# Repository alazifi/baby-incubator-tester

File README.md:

# BABY INCUBATOR TESTER
Proyek ini merupakan kerjasama antara PT. Hana Master Jaya dan PT. Fania Ersa Pratama untuk membuat suatu alat yang digunakan di bidang medis dengan fungsi untuk mengkalibrasi inkubator bayi.

# KOMPATIBILITAS VERSI
<sup>Untuk detail panduan pengelolaan versi [klik disini.](Panduan_Pengelolaan_Versi.md)</sup>

Berikut pasangan versi yang diimplementasikan untuk menghasilkan kinerja alat yang optimal.

| Versi Perangkat |                                 Elektrik                                 |                                     HMI                                      | Koding                                                                    | Mekanik |
|:---------------:|:------------------------------------------------------------------------:|:----------------------------------------------------------------------------:|---------------------------------------------------------------------------|---------|
|   Belum Rilis   | [V5.0.0](Hardware_Development/02_Schematics_and_PCB/PCB_Utama.md#v500-belum-dirilis) | [V3.0.0](Hardware_Development/04_Nextion_HMI/Kode_HMI.md#v300-belum-dirilis) | [V4.0.0](Hardware_Development/03_Code/Kode_Arduino.md#v400-belum-dirilis) | -       |
|     Versi 4     |                                    -                                     |                                      -                                       | -                                                                         | -       |
|     Versi 3     |                                    -                                     |                                      -                                       | -                                                                         | -       |
|     Versi 2     |                                    -                                     |                                      -                                       | -                                                                         | -       |
|     Versi 1     |                                    -                                     |                                      -                                       | -                                                                         | -       |

Untuk dokumentasi skematik dan PCB bisa [klik disini](Hardware_Development/02_Schematics_and_PCB/PCB_Utama.md)!

Untuk dokumentasi koding Arduino bisa [klik disini](Hardware_Development/03_Code/Kode_Arduino.md)!

Untuk dokumentasi UI dari HMI Nextion bisa [klik disini](Hardware_Development/04_Nextion_HMI/Desain_HMI.md)!

## Struktur Direktori Proyek

```bash
project/
│
├── Assembly and Instructions/          # Dokumen untuk produksi
│ ├── 01_Working_Instruction/           # Instruksi untuk produksi
│ └── 02_Checklists/                    # Inspeksi komponen produksi
│
├── Design and Research/                # Data-data terkait riset dalam pengembangan
│ ├── 01_Design_Documents/              # Data rujukan riset dan pengembangan
│ └── 02_Research_Notes/                # Perhitungan nilai komponen
│
├── Final Documentations/               # Dokumentasi terkait pengguna akhir
│ ├── 01_Final_Reports/                 # Laporan akhir setelah produksi
│ ├── 02_User_Manual/                   # Panduan pengguna
│ └── 03_Additional_Resources/          # Sumber tambahan
│
├── Hardware Development/               # Pengembangan terkait perangkat keras
│ ├── 01_BoM_List/                      # Harga pembelian komponen
│ ├── 02_Schematics_and_PCB/            # Desain komponen elektronik
│ ├── 03_Code/                          # Kode firmware untuk PCB
│ └── 04_Nextion_HMI/                   # Desain dan kode untuk HMI
│
├── Past Documents/                     # Data terdahulu sebelum Mei 2023
│
├── Project Management/                 # Manajemen proyek Data-data terkait riset dalam pengembangan
│ ├── 01_Project_Plan/                  # Perencanaan pengerjaan proyek
│ ├── 02_Meetings/                      # Rapat dalam pengerjaan proyek
│ └── 03_Documents/                     # Dokumen terkait manajemen proyek seperti MoM
│
├── Testing and Validation/             # Data-data terkait hasil uji
│ ├── 01_Battery_Testing/               # Data uji baterai
│ ├── 02_Device_Testing/                # Data uji perangkat
│ └── 03_QC_Reports/                    # Laporan QC
│ 
└── README.md # Informasi proyek secara umum, kamu lagi disini!
```
- - - -

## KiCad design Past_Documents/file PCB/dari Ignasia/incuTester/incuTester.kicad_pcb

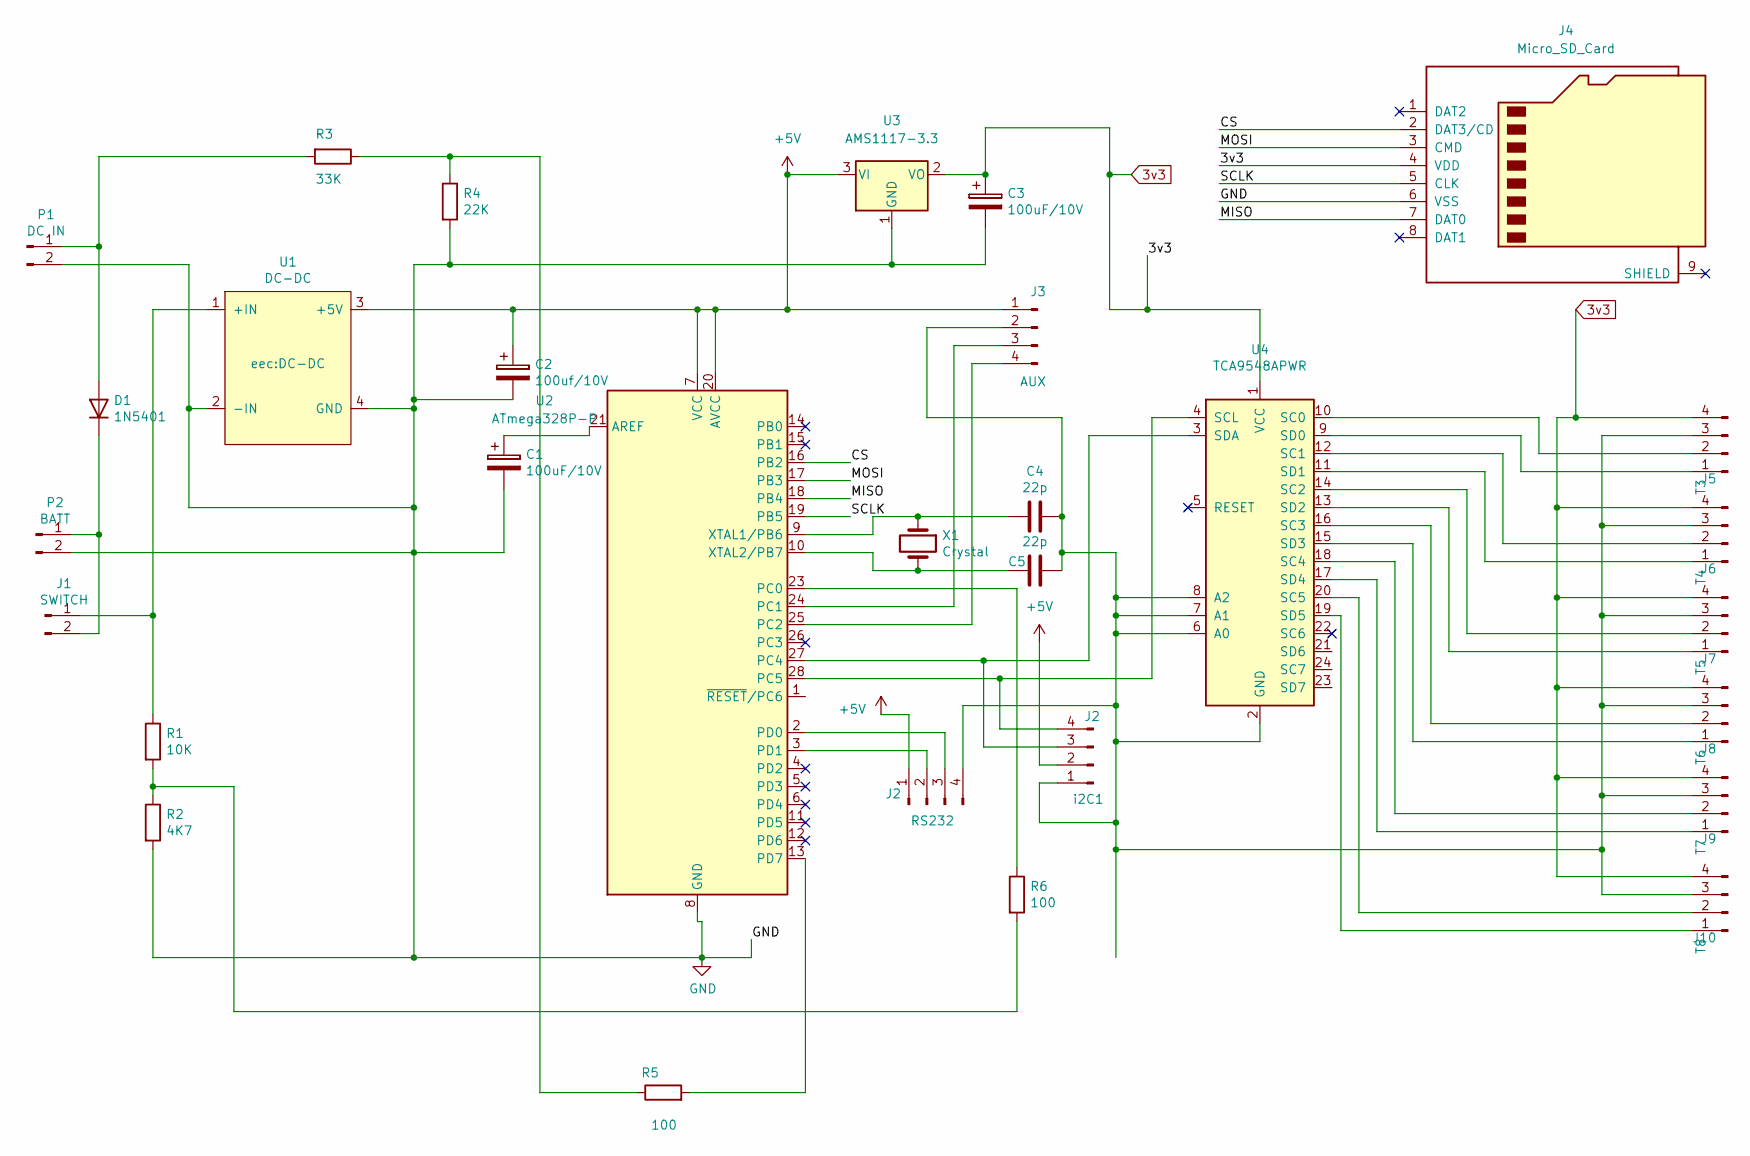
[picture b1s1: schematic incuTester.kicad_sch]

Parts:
C1, C3: 100uF/10V; CP_Radial_D8.0mm_P3.50mm
C2: 100uf/10V; CP_Radial_D8.0mm_P3.50mm
C4, C5: 22p; C_Disc_D3.0mm_W2.0mm_P2.50mm
D1: 1N5401; D_DO-201AD_P15.24mm_Horizontal
J1: SWITCH; PinHeader_1x02_P2.54mm_Vertical
J2: RS232; PinHeader_1x04_P2.54mm_Vertical
J3: AUX; PinHeader_1x04_P2.54mm_Vertical
J4: Micro_SD_Card; microSD_HC_Hirose_DM3AT-SF-PEJM5
J5: T3; PinHeader_1x04_P2.54mm_Vertical
J6: T4; PinHeader_1x04_P2.54mm_Vertical
J7: T5; PinHeader_1x04_P2.54mm_Vertical
J8: T6; PinHeader_1x04_P2.54mm_Vertical
J9: T7; PinHeader_1x04_P2.54mm_Vertical
J10: T8; PinHeader_1x04_P2.54mm_Vertical
P1: DC IN; PinHeader_1x02_P2.54mm_Vertical
P2: BATT; PinHeader_1x02_P2.54mm_Vertical
R1: 10K; R_Axial_DIN0207_L6.3mm_D2.5mm_P10.16mm_Horizontal
R2: 4K7; R_Axial_DIN0207_L6.3mm_D2.5mm_P10.16mm_Horizontal
R3: 33K; R_Axial_DIN0207_L6.3mm_D2.5mm_P10.16mm_Horizontal
R4: 22K; R_Axial_DIN0207_L6.3mm_D2.5mm_P10.16mm_Horizontal
R5, R6: 100; R_Axial_DIN0207_L6.3mm_D2.5mm_P10.16mm_Horizontal
U1: DC-DC
U2: ATmega328P-P; DIP-28_W7.62mm
U3: AMS1117-3.3; SOT-223-3_TabPin2
U4: TCA9548APWR; DIP-24_W15.24mm_LongPads
X1: Crystal; Crystal_HC18-U_Vertical
i2C1: J2; PinHeader_1x04_P2.54mm_Vertical

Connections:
3v3: C3.1, J4.4 (VDD), J5.4, J6.4, J7.4, J8.4, J9.4, J10.4, U3.2 (VO), U4.1 (VCC)
+5V: C2.1, J2.1, J3.1, U1.3 (+5V), U2.7 (VCC), U2.20 (AVCC), i2C1.2; also elsewhere on the board
/CS: J4.2 (DAT3/CD), U2.16 (PB2)
/MISO: J4.7 (DAT0), U2.18 (PB4)
/MOSI: J4.3 (CMD), U2.17 (PB3)
/SCLK: J4.5 (CLK), U2.19 (PB5)
unnamed: D1.2 (A), P1.1, R3.2
unnamed: D1.1 (K), J1.2, P2.1
unnamed: J1.1, R1.1, U1.1 (+IN)
unnamed: J2.2, U2.3 (PD1)
unnamed: J2.3, U2.2 (PD0)
unnamed: J3.3, U2.24 (PC1)
unnamed: J3.4, U2.25 (PC2)
unnamed: J5.1, U4.9 (SD0)
unnamed: J5.2, U4.10 (SC0)
unnamed: J6.1, U4.11 (SD1)
unnamed: J6.2, U4.12 (SC1)
unnamed: J7.1, U4.13 (SD2)
unnamed: J7.2, U4.14 (SC2)
unnamed: J8.1, U4.15 (SD3)
unnamed: J8.2, U4.16 (SC3)
unnamed: J9.1, U4.17 (SD4)
unnamed: J9.2, U4.18 (SC4)
unnamed: J10.1, U4.19 (SD5)
unnamed: J10.2, U4.20 (SC5)
unnamed: R1.2, R2.1, R6.2
unnamed: R3.1, R4.1, R5.1
unnamed: C1.1, U2.21 (AREF)
unnamed: R6.1, U2.23 (PC0)
unnamed: U2.27 (PC4), U4.3 (SDA), i2C1.3
unnamed: U2.28 (PC5), U4.4 (SCL), i2C1.4
unnamed: R5.2, U2.13 (PD7)
unnamed: C4.1, U2.9 (XTAL1/PB6), X1.1
unnamed: C5.1, U2.10 (XTAL2/PB7), X1.2
RST: U2.1 (~RESET/PC6); also elsewhere on the board

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
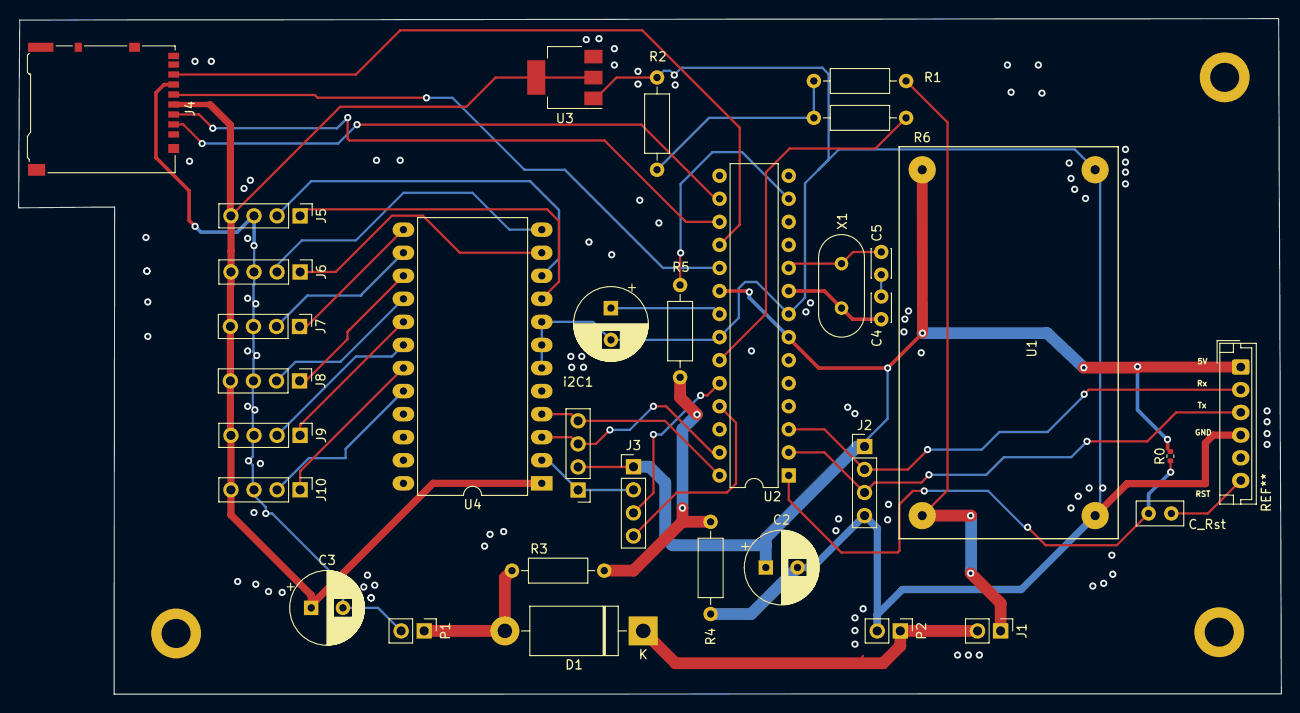
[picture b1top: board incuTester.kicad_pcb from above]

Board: 2 copper layers, 139.1 x 74.4 mm, 32 parts (0 on the bottom side), 36 nets.

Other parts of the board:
C_Rst: 0.1uF/10V; C_Disc_D5.0mm_W2.5mm_P2.50mm
R0: 10k; R_0402_1005Metric

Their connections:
+5V: R0.2; also elsewhere on the board
RST: C_Rst.1, R0.1; also elsewhere on the board

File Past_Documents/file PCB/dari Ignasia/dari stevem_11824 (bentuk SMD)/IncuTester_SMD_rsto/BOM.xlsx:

Column1 | Column2 | Column3 | Column4 | Column5 | Column6 | Column7 | Column8 | Column9 | Column10
Date: | 29/11/2023 08:27:42
Tool: | Eeschema 7.0.6
Generator: | C:\Program Files\KiCad\7.0\bin\scripting\plugins/bom_csv_grouped_by_value.py
Component Count: | 30
Collated Components:
Item | Manufacturer Part | Manufacturer / Supplier | Qty | Reference(s) | Value | LibPart | Footprint | Datasheet | Link
1 | 04EC2054 | KNSCHA | 2 | C1, C3 | 100uF/10V | INCUersa-rescue:CP-Device | Capacitor_THT:CP_Radial_D8.0mm_P3.50mm
2 | 04EC2054 | KNSCHA | 1 | C2 | 100uf/10V | INCUersa-rescue:CP-Device | Capacitor_THT:CP_Radial_D8.0mm_P3.50mm
3 | CC1H220KA1EDCH4B1100 | Dersonic | 2 | C4, C5 | 22p | Device:C | Capacitor_THT:C_Disc_D3.0mm_W2.0mm_P2.50mm | ~
4 | 1N5401 | MDD (Microdiode Electronics) | 1 | D1 | 1N5401 | Diode:1N5401 | Diode_THT:D_DO-201AD_P15.24mm_Horizontal | http://www.vishay.com/docs/88516/1n5400.pdf
5 | B4B-XH-A(LF)(SN) | JST | 1 | i2C1 | J2 | Connector:Conn_01x04_Male | Connector_PinHeader_2.54mm:PinHeader_1x04_P2.54mm_Vertical | ~
6 | B2B-XH-A(LF)(SN) | JST | 1 | J1 | SWITCH | Connector:Conn_01x02_Male | Connector_PinHeader_2.54mm:PinHeader_1x02_P2.54mm_Vertical | ~
7 | B4B-XH-A(LF)(SN) | JST | 1 | J2 | RS232 | Connector:Conn_01x04_Male | Connector_PinHeader_2.54mm:PinHeader_1x04_P2.54mm_Vertical | ~
8 | B4B-XH-A(LF)(SN) | JST | 1 | J3 | AUX | Connector:Conn_01x04_Male | Connector_PinHeader_2.54mm:PinHeader_1x04_P2.54mm_Vertical | ~
9 | DM3AT-SF-PEJM5 | Hirose | 1 | J4 | Micro_SD_Card | Connector:Micro_SD_Card | Connector_Card:microSD_HC_Hirose_DM3AT-SF-PEJM5 | http://katalog.we-online.de/em/datasheet/693072010801.pdf
10 | B4B-XH-A(LF)(SN) | JST | 1 | J5 | T3 | Connector:Conn_01x04_Male | Connector_PinHeader_2.54mm:PinHeader_1x04_P2.54mm_Vertical | ~
11 | B4B-XH-A(LF)(SN) | JST | 1 | J6 | T4 | Connector:Conn_01x04_Male | Connector_PinHeader_2.54mm:PinHeader_1x04_P2.54mm_Vertical | ~
12 | B4B-XH-A(LF)(SN) | JST | 1 | J7 | T5 | Connector:Conn_01x04_Male | Connector_PinHeader_2.54mm:PinHeader_1x04_P2.54mm_Vertical | ~
13 | B4B-XH-A(LF)(SN) | JST | 1 | J8 | T6 | Connector:Conn_01x04_Male | Connector_PinHeader_2.54mm:PinHeader_1x04_P2.54mm_Vertical | ~
14 | B4B-XH-A(LF)(SN) | JST | 1 | J9 | T7 | Connector:Conn_01x04_Male | Connector_PinHeader_2.54mm:PinHeader_1x04_P2.54mm_Vertical | ~
15 | B4B-XH-A(LF)(SN) | JST | 1 | J10 | T8 | Connector:Conn_01x04_Male | Connector_PinHeader_2.54mm:PinHeader_1x04_P2.54mm_Vertical | ~
16 | B2B-XH-A(LF)(SN) | JST | 1 | P1 | DC IN | Connector:Conn_01x02_Male | Connector_PinHeader_2.54mm:PinHeader_1x02_P2.54mm_Vertical | ~
17 | B2B-XH-A(LF)(SN) | JST | 1 | P2 | BATT | Connector:Conn_01x02_Male | Connector_PinHeader_2.54mm:PinHeader_1x02_P2.54mm_Vertical | ~
18 | Resistor 10kOhm, minimal 100mW, THT |  | 1 | R1 | 10K | Device:R | Resistor_THT:R_Axial_DIN0207_L6.3mm_D2.5mm_P10.16mm_Horizontal | ~
19 | Resistor 4700Ohm, minimal 100mW, THT |  | 1 | R2 | 4K7 | Device:R | Resistor_THT:R_Axial_DIN0207_L6.3mm_D2.5mm_P10.16mm_Horizontal | ~
20 | Resistor 33kOhm, minimal 250mW, THT |  | 1 | R3 | 33K | Device:R | Resistor_THT:R_Axial_DIN0207_L6.3mm_D2.5mm_P10.16mm_Horizontal | ~
21 | Resistor 22kOhm, minimal 250mW, THT |  | 1 | R4 | 22K | Device:R | Resistor_THT:R_Axial_DIN0207_L6.3mm_D2.5mm_P10.16mm_Horizontal | ~
22 | Resistor 100Ohm, minimal 100mW, THT |  | 2 | R5, R6 | 100 | Device:R | Resistor_THT:R_Axial_DIN0207_L6.3mm_D2.5mm_P10.16mm_Horizontal | ~
23 | LM2596S DC To DC Buck Converter | Shenzhen Robotlinking Technology Co., Ltd. | 1 | U1 | DC-DC | INCUersa-rescue:DC-DC-arduino_module | eec:DC-DC |  | https://www.alibaba.com/product-detail/LM2596-LM2596S-DC-To-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
24 | ATMEGA328P-PU | Microchip Tech | 1 | U2 | ATmega328P-P | MCU_Microchip_ATmega:ATmega328P-P | Package_DIP:DIP-28_W7.62mm | http://ww1.microchip.com/downloads/en/DeviceDoc/ATmega328_P%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
25 | AMS1117-3.3 | Advanced Monolithic Systems | 1 | U3 | AMS1117-3.3 | Regulator_Linear:AMS1117-3.3 | Package_TO_SOT_SMD:SOT-223-3_TabPin2 | http://www.advanced-monolithic.com/pdf/ds1117.pdf
26 | TCA9548A I2C Multi-channel Multiplexer | Shenzhen Zida Times Technology Co., Ltd. | 1 | U4 | TCA9548APWR | INCUersa-rescue:TCA9548APWR-Interface_Expansion | Package_DIP:DIP-24_W15.24mm_LongPads |  | https://www.alibaba.com/product-detail/TCA9548A-1-To-8-I2C-8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
27 | X49SD16MSD2SC | YXC | 1 | X1 | Crystal | Device:Crystal | Crystal:Crystal_HC18-U_Vertical | ~
28 | KS104M050C07RR0VH2FP0 | CX(Dongguan Chengxing Elec) | 1 | C_Rst | 0.1uF
29 | B6B-XH-A(LF)(SN) | JST | 1
 | Resistor 10kOhm, minimal 100mW, SMD |  | 1 | R0

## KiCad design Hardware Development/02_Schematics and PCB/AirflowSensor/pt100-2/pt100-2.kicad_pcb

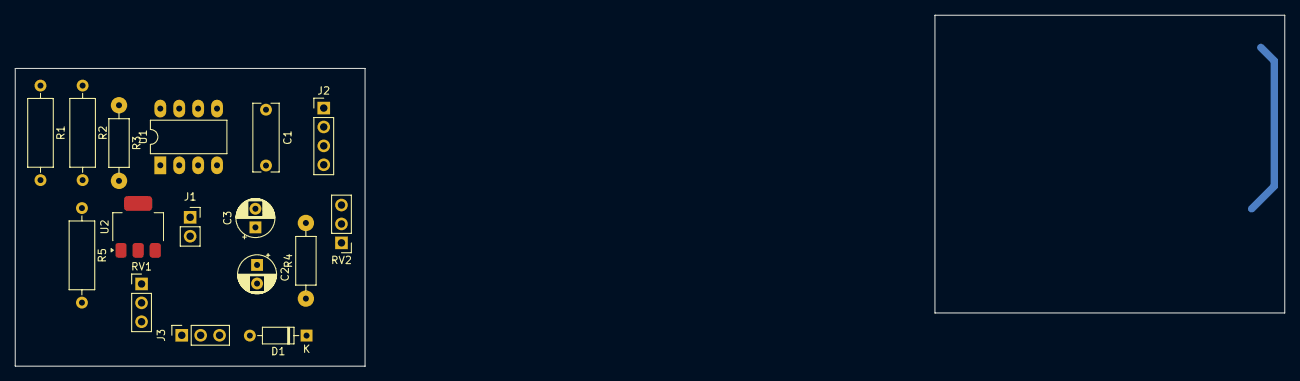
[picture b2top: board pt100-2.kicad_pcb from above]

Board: 2 copper layers, 170.6 x 47.1 mm, 16 parts (0 on the bottom side), 12 nets.

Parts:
C1: 220nF; C_Rect_L9.0mm_W3.3mm_P7.50mm_MKT
C2: 100uF 16 V; CP_Radial_D5.0mm_P2.50mm
C3: 47uF 16 V; CP_Radial_D5.0mm_P2.50mm
D1: 1N60; D_DO-35_SOD27_P7.62mm_Horizontal
J1: PT100 Class A; PinSocket_1x02_P2.54mm_Vertical
J2: OUT; PinHeader_1x04_P2.54mm_Vertical
J3: MAX 4466; PinSocket_1x03_P2.54mm_Vertical
R1, R2: 120R 1W 1%; R_Axial_DIN0309_L9.0mm_D3.2mm_P12.70mm_Horizontal
R3: 2K2 1/4W 1%; R_Axial_DIN0207_L6.3mm_D2.5mm_P10.16mm_HorBigPad
R4: 4K7 1/4W 1%; R_Axial_DIN0207_L6.3mm_D2.5mm_P10.16mm_HorBigPad
R5: 47R 1W 1%; R_Axial_DIN0309_L9.0mm_D3.2mm_P12.70mm_Horizontal
RV1: 100R; PinHeader_1x03_P2.54mm_Vertical
RV2: 50K; PinHeader_1x03_P2.54mm_Vertical
U1: TL072; DIP-8_W7.62mm_LongPads
U2: AMS1117-3.3; SOT-223-3_TabPin2

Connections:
GND: C1.2, C2.2, C3.2, J1.2, J2.4, J3.2, RV1.3, RV2.3, U1.4 (V-), U1.5 (+), U2.1 (GND)
unnamed: C1.1, J2.2, R3.1, U1.1
unnamed: C3.1, R4.2, RV2.2
unnamed: D1.2 (A), J3.3
unnamed: D1.1 (K), R4.1
unnamed: J2.3, RV2.1
unnamed: R5.2, RV1.1, RV1.2
unnamed: R2.2, R5.1, U1.3 (+)
unnamed: J1.1, R1.2, R3.2, U1.2 (-)
unnamed: U1.6 (-), U1.7
unnamed: J2.1, R1.1, R2.1, U1.8 (V+), U2.3 (VI)
unnamed: C2.1, J3.1, U2.2 (VO)

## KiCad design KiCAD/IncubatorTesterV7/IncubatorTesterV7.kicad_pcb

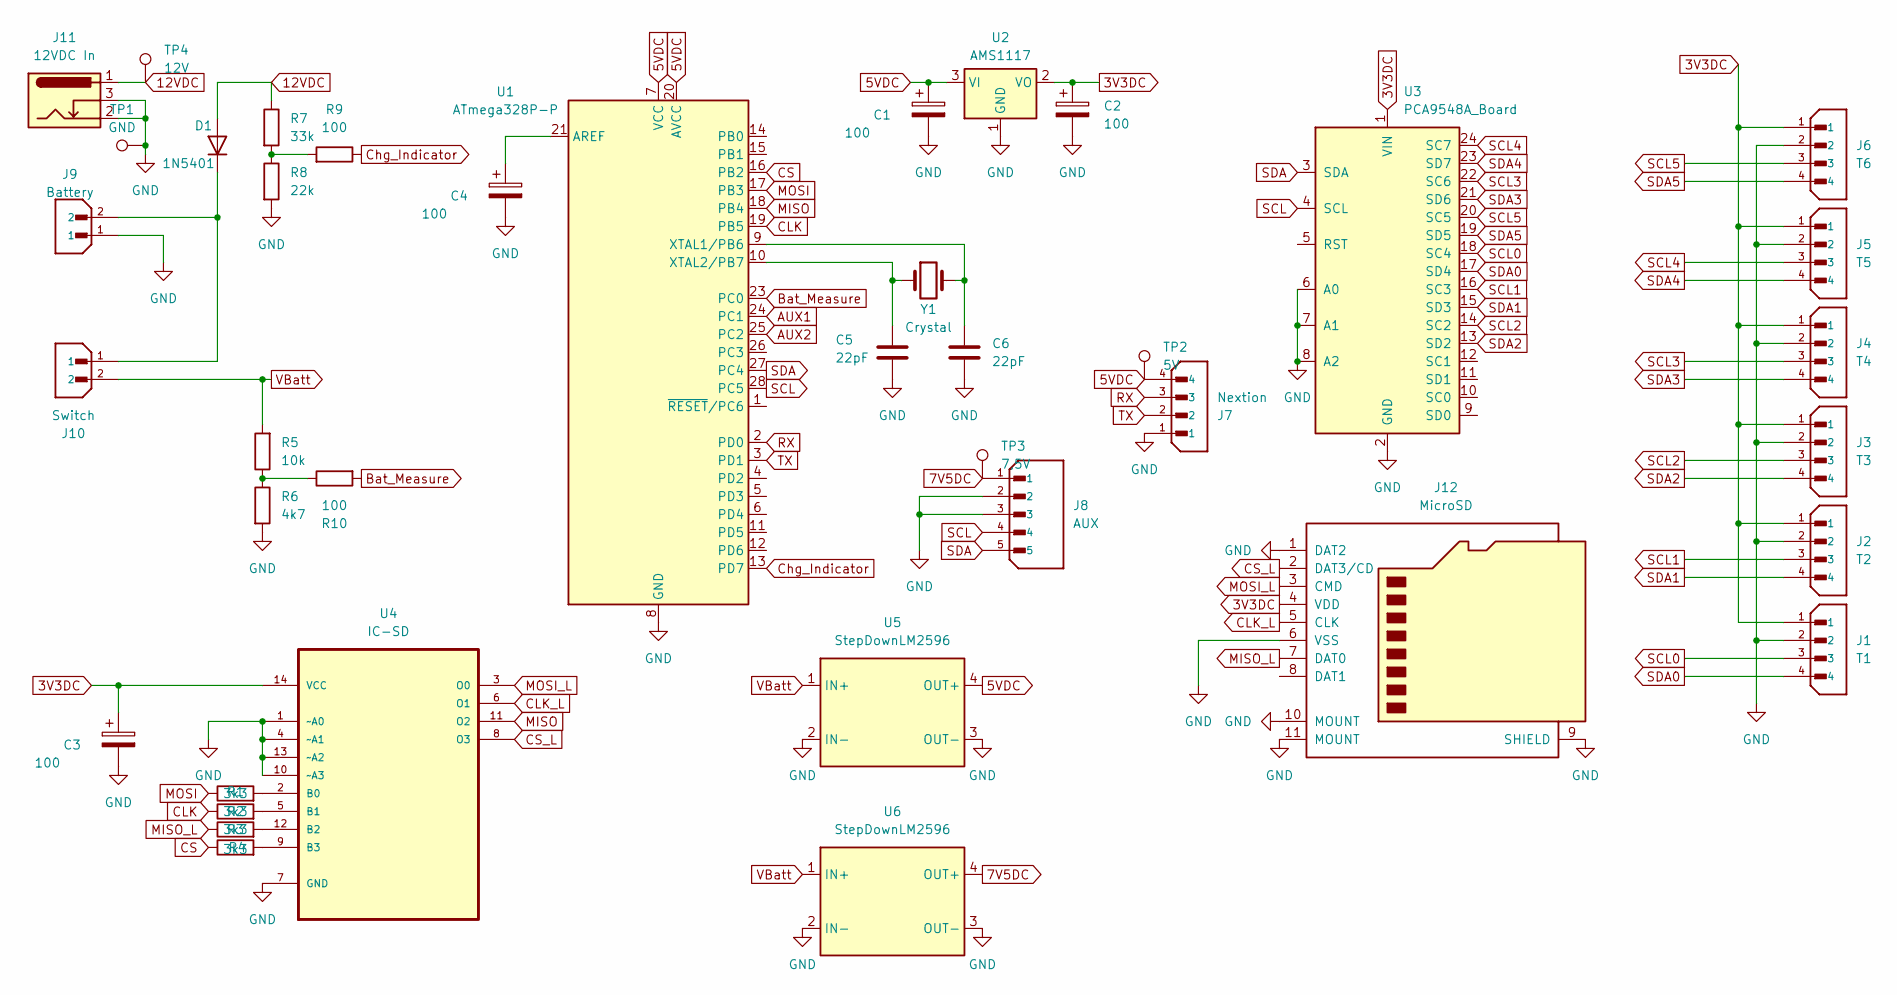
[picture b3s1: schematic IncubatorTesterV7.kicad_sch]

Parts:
C1, C2, C3, C4: 100; C_Radial
C5, C6: 22pF; C_Disc_D3.0mm_W1.6mm_P2.50mm
D1: 1N5401; D_DO-201AD_P15.24mm_Horizontal
J1: T1; JST_B4B-XH-A_LF__SN_
J2: T2; JST_B4B-XH-A_LF__SN_
J3: T3; JST_B4B-XH-A_LF__SN_
J4: T4; JST_B4B-XH-A_LF__SN_
J5: T5; JST_B4B-XH-A_LF__SN_
J6: T6; JST_B4B-XH-A_LF__SN_
J7: Nextion; JST_B4B-XH-A_LF__SN_
J8: AUX; JST_B5B-XH-A_LF__SN_; PARTREV 7/4/21
J9: Battery; JST_XH_S2B-XH-A_1x02_P2.50mm_Horizontal
J10: Switch; JST_B2B-XH-A
J11: 12VDC In; BarrelJack_Horizontal
J12: MicroSD; HRS_DM3AT-SF-PEJM5; PARTREV 20200913
R1, R2, R3, R4: 3k3; R_Axial
R5: 10k; R_Axial
R6: 4k7; R_Axial
R7: 33k; R_Axial
R8: 22k; R_Axial
R9, R10: 100; R_Axial
TP1: GND; TestPoint_Pad_D2.0mm
TP2: 5V; TestPoint_Pad_D2.0mm
TP3: 7,5V; TestPoint_Pad_D2.0mm
TP4: 12V; TestPoint_Pad_D2.0mm
U1: ATmega328P-P; DIP-28_W7.62mm
U2: AMS1117; SOT-223-3_TabPin2
U3: PCA9548A_Board; PCA9548A
U4: IC-SD; SOIC127P600X175-14N; MPN 74VHC125M
U5, U6: StepDownLM2596; Step_Down_DCDC
Y1: Crystal; Crystal_HC49-4H_Vertical

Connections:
3V3DC: C2.1, C3.1, J1.1, J2.1, J3.1, J4.1, J5.1, J6.1, J12.4 (VDD), U2.2 (VO), U3.1 (VIN), U4.14 (VCC)
5VDC: C1.1, J7.4, TP2.1, U1.7 (VCC), U1.20 (AVCC), U2.3 (VI), U5.4 (OUT+)
7V5DC: J8.1, TP3.1, U6.4 (OUT+)
12VDC: D1.2 (A), J11.1, R7.1, TP4.1
AUX1: U1.24 (PC1)
AUX2: U1.25 (PC2)
Bat_Measure: R10.2, U1.23 (PC0)
CLK: R2.1, U1.19 (PB5)
CLK_L: J12.5 (CLK), U4.6 (O1)
CS: R4.1, U1.16 (PB2)
CS_L: J12.2 (DAT3/CD), U4.8 (O3)
Chg_Indicator: R9.1, U1.13 (PD7)
GND: C1.2, C2.2, C3.2, C4.2, C5.2, C6.2, J1.2, J2.2, J3.2, J4.2, J5.2, J6.2, J7.1, J8.2, J8.3, J9.1, J11.2, J11.3, J12.1 (DAT2), J12.6 (VSS), J12.9 (SHIELD), J12.10 (MOUNT), J12.11 (MOUNT), R6.2, R8.2, TP1.1, U1.8 (GND), U1.22 (GND), U2.1 (GND), U3.2 (GND), U3.6 (A0), U3.7 (A1), U3.8 (A2), U4.1 (~A0), U4.4 (~A1), U4.7 (GND), U4.10 (~A3), U4.13 (~A2), U5.2 (IN-), U5.3 (OUT-), U6.2 (IN-), U6.3 (OUT-)
MISO: U1.18 (PB4), U4.11 (O2)
MISO_L: J12.7 (DAT0), R3.1
MOSI: R1.1, U1.17 (PB3)
MOSI_L: J12.3 (CMD), U4.3 (O0)
unnamed: D1.1 (K), J9.2, J10.1
unnamed: R7.2, R8.1, R9.2
unnamed: R5.1, R6.1, R10.1
unnamed: C4.1, U1.21 (AREF)
unnamed: C6.1, U1.9 (XTAL1/PB6), Y1.2
unnamed: C5.1, U1.10 (XTAL2/PB7), Y1.1
unnamed: R1.2, U4.2 (B0)
unnamed: R2.2, U4.5 (B1)
unnamed: R3.2, U4.12 (B2)
unnamed: R4.2, U4.9 (B3)
RX: J7.3, U1.2 (PD0)
SCL: J8.4, U1.28 (PC5), U3.4 (SCL)
SCL0: J1.3, U3.18 (SC4)
SCL1: J2.3, U3.16 (SC3)
SCL2: J3.3, U3.14 (SC2)
SCL3: J4.3, U3.22 (SC6)
SCL4: J5.3, U3.24 (SC7)
SCL5: J6.3, U3.20 (SC5)
SDA: J8.5, U1.27 (PC4), U3.3 (SDA)
SDA0: J1.4, U3.17 (SD4)
SDA1: J2.4, U3.15 (SD3)
SDA2: J3.4, U3.13 (SD2)
SDA3: J4.4, U3.21 (SD6)
SDA4: J5.4, U3.23 (SD7)
SDA5: J6.4, U3.19 (SD5)
TX: J7.2, U1.3 (PD1)
VBatt: J10.2, R5.2, U5.1 (IN+), U6.1 (IN+)

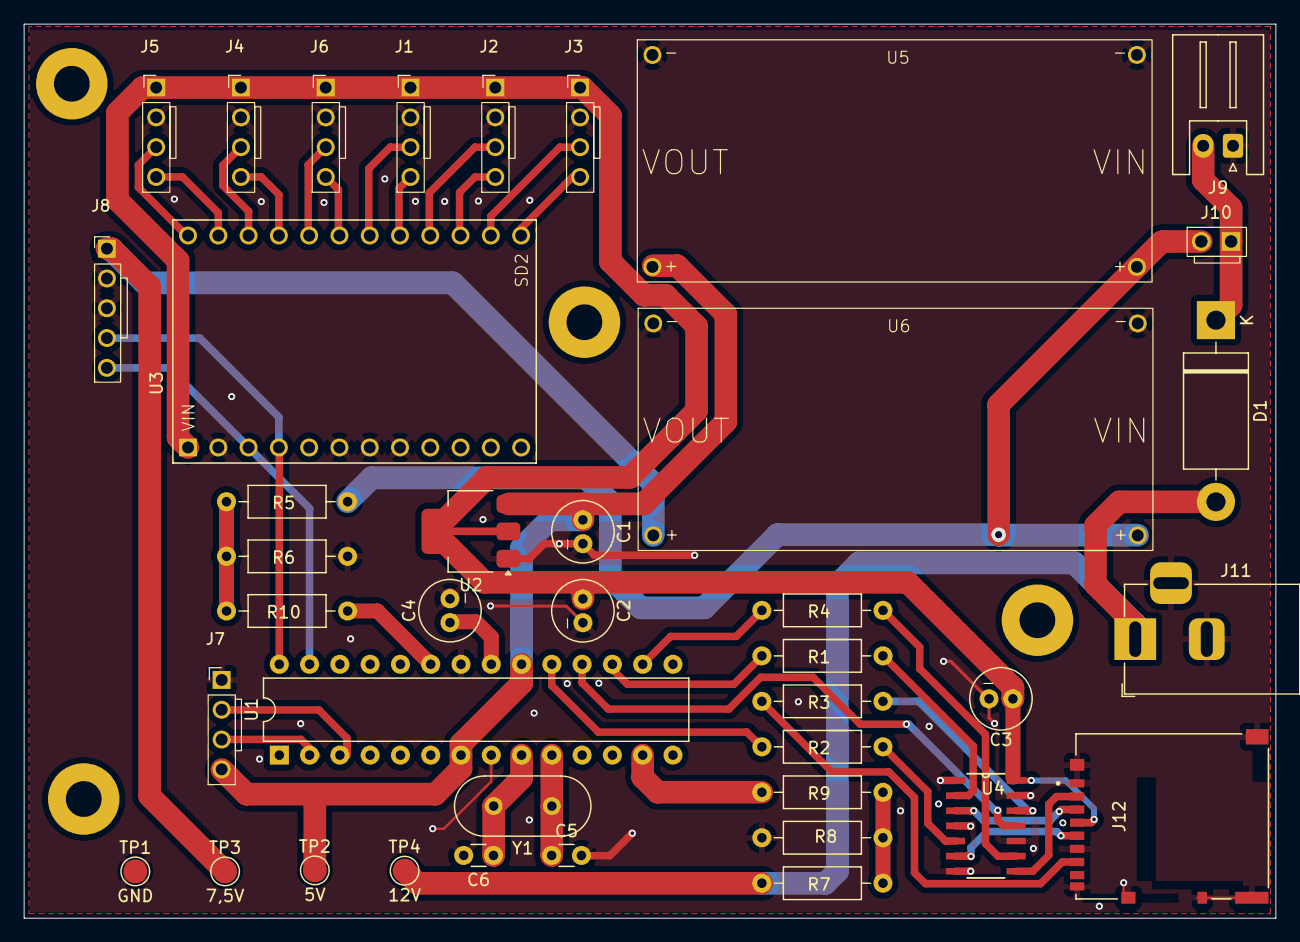
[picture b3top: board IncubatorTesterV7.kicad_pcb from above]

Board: 2 copper layers, 105.0 x 75.0 mm, 40 parts (0 on the bottom side), 42 nets.

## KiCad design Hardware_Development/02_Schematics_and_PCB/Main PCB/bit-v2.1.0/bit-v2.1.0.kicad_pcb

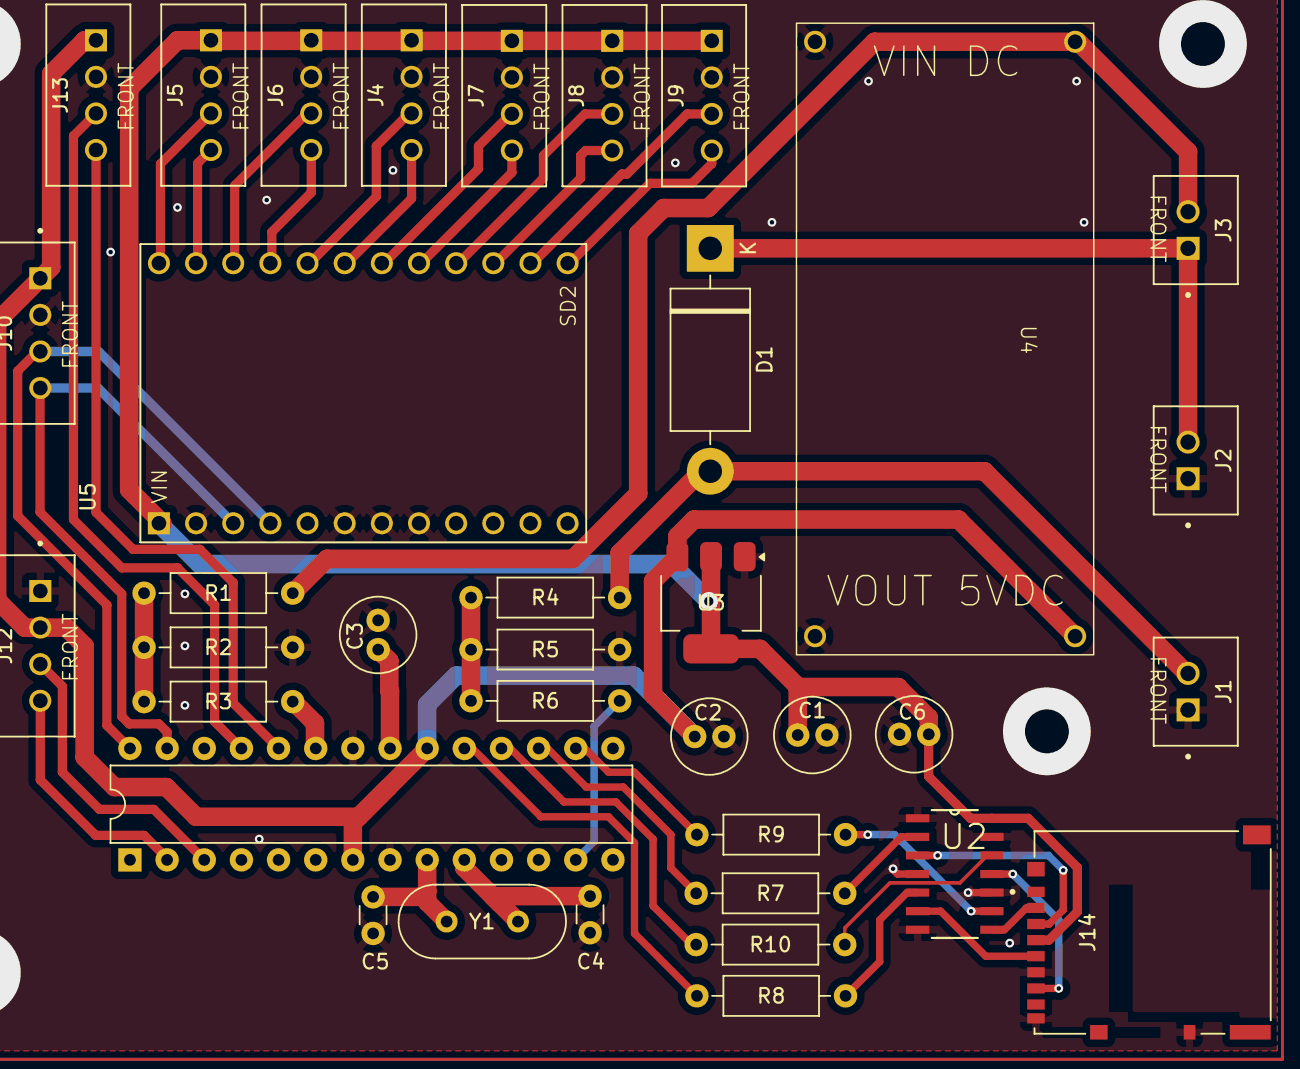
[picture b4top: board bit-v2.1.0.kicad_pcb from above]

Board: 2 copper layers, 36 parts (0 on the bottom side), 43 nets.

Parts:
C1, C2, C3, C6: 100uF; C_Radial_D5.0mm_H11.0mm_P2.00mm
C4, C5: 22pF; C_Disc_D3.0mm_W1.6mm_P2.50mm
D1: 1N5401; D_DO-201AD_P15.24mm_Horizontal
J1: 12VDC In; JST_B2B-XH-A
J2: Battery; JST_B2B-XH-A
J3: Switch; JST_B2B-XH-A
J4: T6; JST_B4B-XH-A_LF__SN_
J5: T5; JST_B4B-XH-A_LF__SN_
J6: T4; JST_B4B-XH-A_LF__SN_
J7: T3; JST_B4B-XH-A_LF__SN_
J8: T2; JST_B4B-XH-A_LF__SN_
J9: T1; JST_B4B-XH-A_LF__SN_
J10: I2C; JST_B4B-XH-A_LF__SN_
J12: Display; JST_B4B-XH-A_LF__SN_
J13: AUX; JST_B4B-XH-A_LF__SN_
J14: MicroSD; HRS_DM3AT-SF-PEJM5
R1: 10k; R_Axial_DIN0207_L6.3mm_D2.5mm_P10.16mm_Horizontal
R2: 4k7; R_Axial_DIN0207_L6.3mm_D2.5mm_P10.16mm_Horizontal
R3, R6: 100; R_Axial_DIN0207_L6.3mm_D2.5mm_P10.16mm_Horizontal
R4: 33k; R_Axial_DIN0207_L6.3mm_D2.5mm_P10.16mm_Horizontal
R5: 22k; R_Axial_DIN0207_L6.3mm_D2.5mm_P10.16mm_Horizontal
R7, R8, R9, R10: 3k3; R_Axial_DIN0207_L6.3mm_D2.5mm_P10.16mm_Horizontal
U1: ATmega328P-P; DIP-28_W7.62mm
U2: IC-SD; SOIC127P600X175-14N
U3: AMS1117; SOT-223-3_TabPin2
U4: Step Down DC - DC; Step_Down_DCDC
U5: PCA9548A_Board; PCA9548A
Y1: Crystal; Crystal_HC49-4H_Vertical

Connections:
3V3DC: C1.1, C6.1, J4.1, J5.1, J6.1, J7.1, J8.1, J9.1, J14.4 (VDD), U2.14 (VCC), U3.2 (VO), U5.1 (VIN)
5VDC: C2.1, J10.1, J12.2, J13.1, U1.7 (VCC), U1.20 (AVCC), U3.3 (VI), U4.4 (OUT-)
AUX1: J13.4, U1.24 (PC1)
AUX2: J13.3, U1.25 (PC2)
Bat_Measure: R3.1, U1.23 (PC0)
CLK: R8.1, U1.19 (PB5)
CLK_L: J14.5 (CLK), U2.6 (O1)
CS: R9.1, U1.16 (PB2)
CS_L: J14.2 (DAT3/CD), U2.8 (O3)
Chg_Indicator: R6.1, U1.13 (PD7)
GND: C1.2, C2.2, C3.2, C4.2, C5.2, C6.2, J1.1, J2.1, J4.2, J5.2, J6.2, J7.2, J8.2, J9.2, J10.2, J12.1, J13.2, J14.6 (VSS), J14.9 (SHIELD), R2.2, R5.2, U1.8 (GND), U1.22 (GND), U2.1 (~A0), U2.4 (~A1), U2.7 (GND), U2.10 (~A3), U2.13 (~A2), U3.1 (GND), U4.2 (IN-), U4.3 (OUT+), U5.2 (GND), U5.6 (A0), U5.7 (A1), U5.8 (A2)
MISO: R10.1, U1.18 (PB4)
MISO_L: J14.7 (DAT0), U2.11 (O2)
MOSI: R7.1, U1.17 (PB3)
MOSI_L: J14.3 (CMD), U2.3 (O0)
unnamed: D1.2 (A), J1.2, R4.1
unnamed: D1.1 (K), J2.2, J3.1
unnamed: R1.2, R2.1, R3.2
unnamed: R4.2, R5.1, R6.2
unnamed: C3.1, U1.21 (AREF)
unnamed: C5.1, U1.9 (XTAL1/PB6), Y1.2
unnamed: C4.1, U1.10 (XTAL2/PB7), Y1.1
unnamed: R7.2, U2.2 (B0)
unnamed: R8.2, U2.5 (B1)
unnamed: R10.2, U2.12 (B2)
unnamed: R9.2, U2.9 (B3)
RX: J12.4, U1.2 (PD0)
SCL: J10.3, U1.28 (PC5), U5.4 (SCL)
SCL0: J9.3, U5.14 (SC2)
SCL1: J8.3, U5.16 (SC3)
SCL2: J7.3, U5.18 (SC4)
SCL3: J6.3, U5.22 (SC6)
SCL4: J5.3, U5.24 (SC7)
SCL5: J4.3, U5.20 (SC5)
SDA: J10.4, U1.27 (PC4), U5.3 (SDA)
SDA0: J9.4, U5.13 (SD2)
SDA1: J8.4, U5.15 (SD3)
SDA2: J7.4, U5.17 (SD4)
SDA3: J6.4, U5.21 (SD6)
SDA4: J5.4, U5.23 (SD7)
SDA5: J4.4, U5.19 (SD5)
TX: J12.3, U1.3 (PD1)
VBatt: J3.2, R1.1, U4.1 (IN+)

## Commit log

2024-07-31 first commit - confidential
2024-07-31 Add video simulation
2024-12-06 add link
2024-12-06 add directory
2024-12-07 adding version
2024-12-07 [feat]: add button
2024-12-07 table revision
2024-12-07 [docs]: table formatting
2024-12-07 [docs]: table
2024-12-07 [docs]: add description of device
2024-12-07 [docs]: change doc name
2024-12-07 [docs]: add language
2024-12-07 [docs]: add docs
2024-12-10 [docs]: change backslash
2024-12-13 [docs]: update docs
2024-12-13 [docs]: add table
2024-12-13 [docs]: add unreleased version
2024-12-13 [docs]:add unreleased hardware
2024-12-16 [docs]: refined docs
2025-06-13 [add] one page as battery low indicator
